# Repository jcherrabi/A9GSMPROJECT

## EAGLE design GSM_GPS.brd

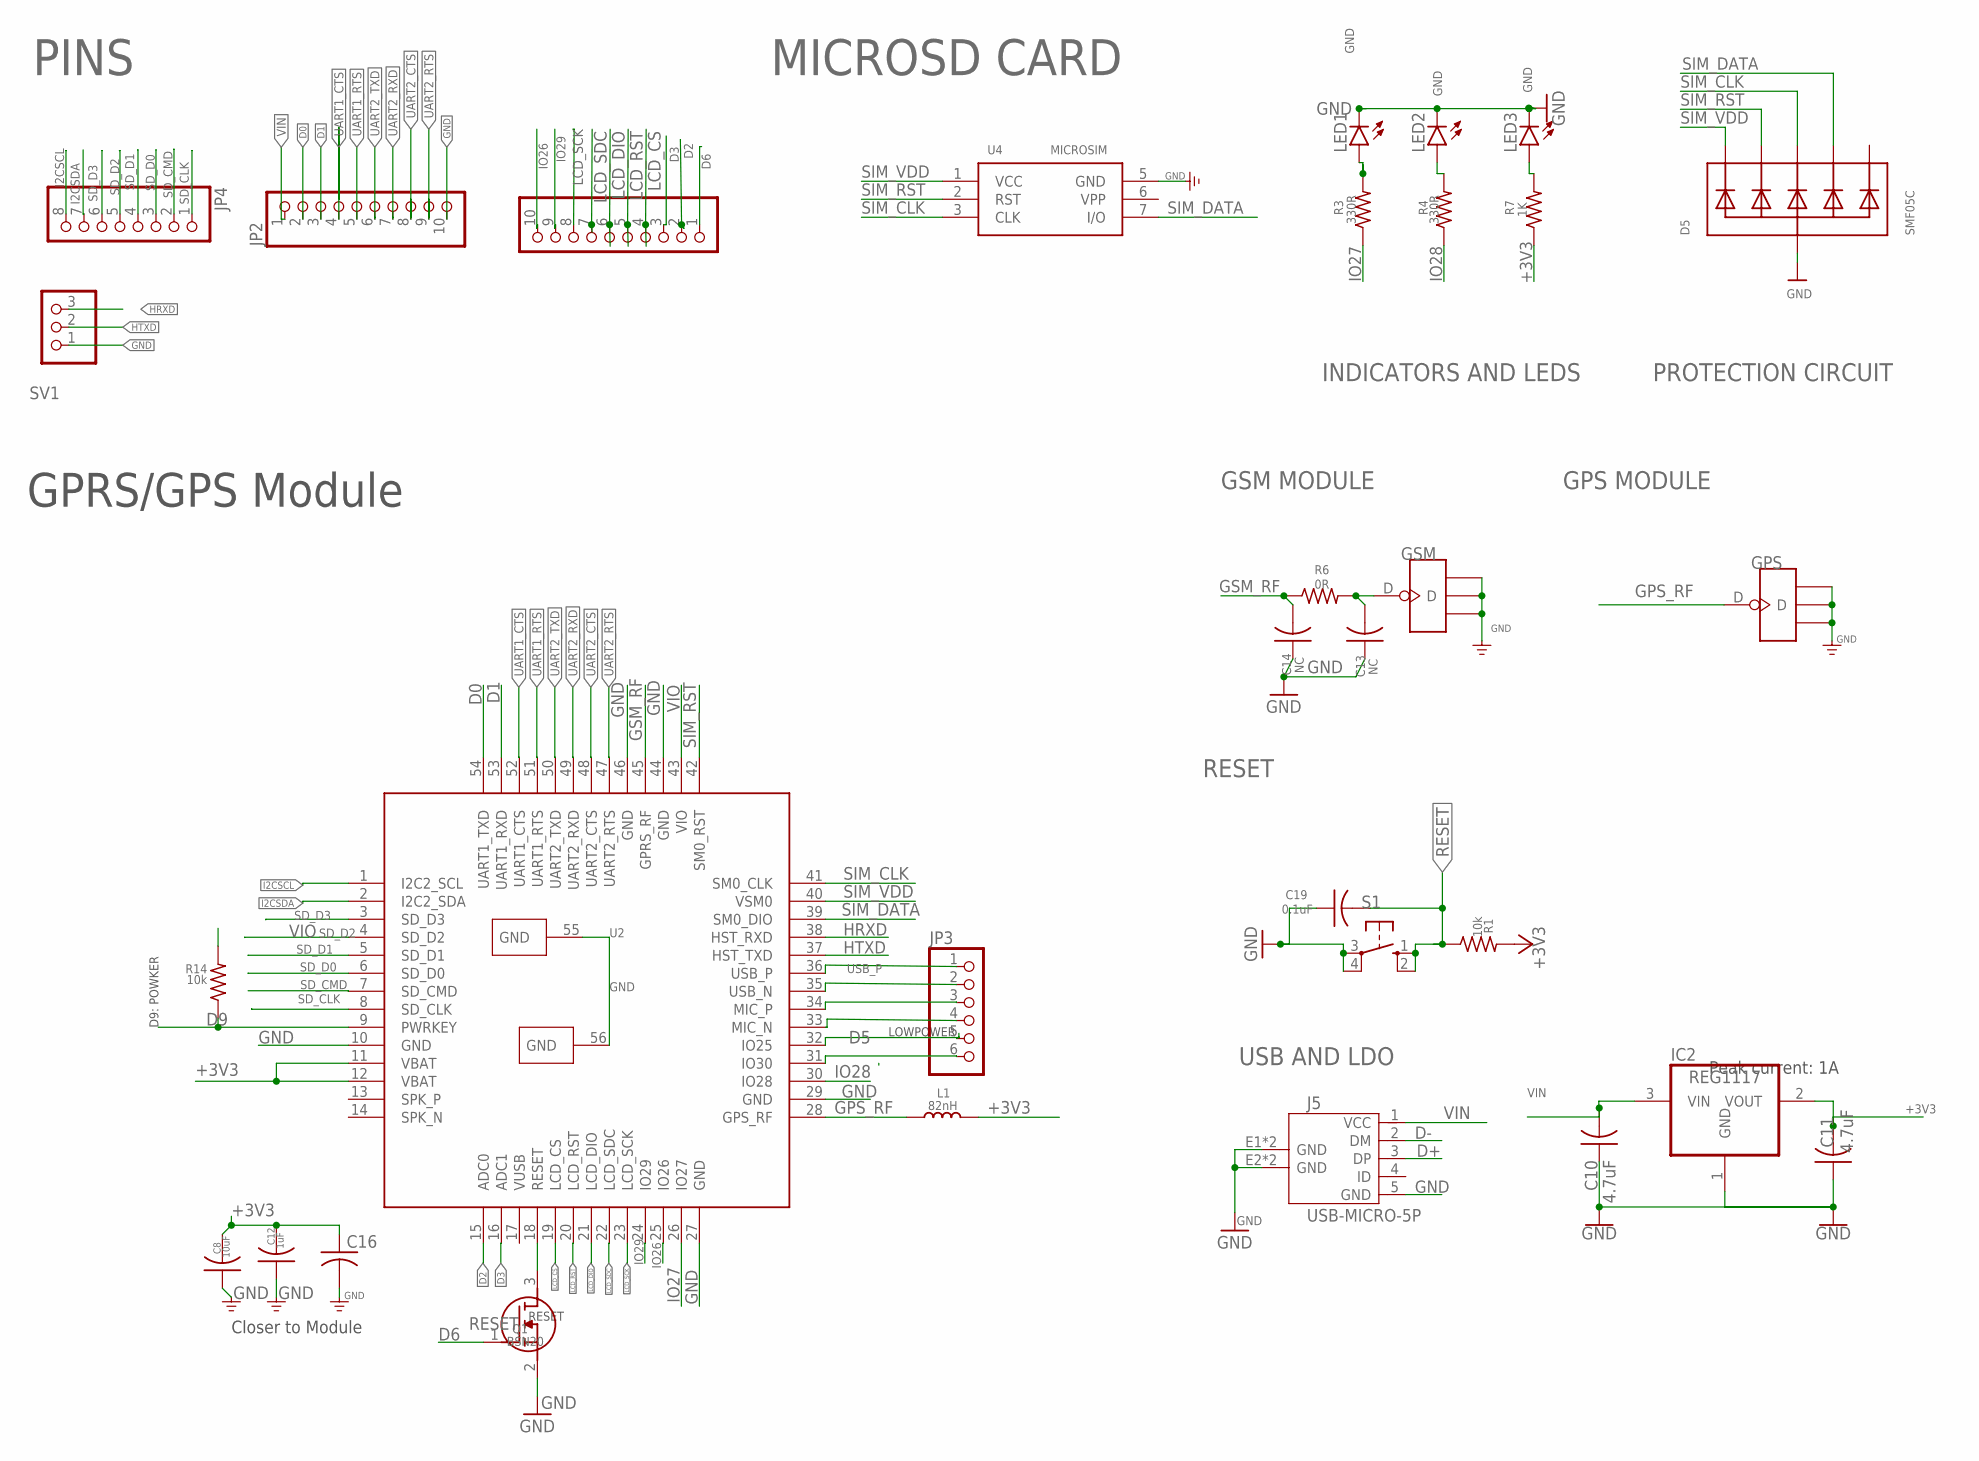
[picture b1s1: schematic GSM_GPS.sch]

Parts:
C8: 10uF; C0805
C10, C11: 4.7uF; C0805
C12: 1uF; C0805
C13, C14: NC; C0805
C16: 100uF; C0805
C19: 0.1uF; C0805
D5: SMF05C; SOT363
GPS: ANTENNA-U-FL; 4P-U-FL
GSM: ANTENNA-U-FL; 4P-U-FL
IC2: REG1117; SOT223
J2: PINHD-1X10; 1X10
J5: USB-MICRO-5P; MICRO-USB-5P
JP2: PINHD-1X10; 1X10
JP3: PINHD-1X6; 1X06
JP4: PINHD-1X8; 1X08
L1: 82nH; L0603
LED1, LED2, LED3: LEDCHIPLED_0805; CHIPLED_0805
Q1: BSN20; SOT95P237X112-3N
R1, R14: 10k; R0805
R3, R4: 330R; R0805
R6: 0R; R0805
R7: 1K; R0805
S1: 10-XX; B3F-10XX
SV1: PINHD-1X3; 1X03
U2: A9G
U4: MICROSIM

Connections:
+3V3: C8.2, C11.2, C12.2, C16.1, IC2.2 (VOUT), L1.2, R1.2, R7.1, U2.11 (VBAT), U2.12 (VBAT)
D0: JP2.2, U2.54 (UART1_TXD)
D1: JP2.3, U2.53 (UART1_RXD)
D2: J2.2, U2.15 (ADC0)
D3: J2.3, U2.16 (ADC1)
D5: JP3.5, U2.32 (IO25)
D6: J2.1, Q1.1 (G)
D9: R14.1, U2.9 (PWRKEY)
D+: J5.3 (DP)
D-: J5.2 (DM)
GND: C8.1, C10.1, C11.1, C12.1, C13.1, C14.1, C16.2, C19.1, D5.2 (A), GPS.GND1, GPS.GND2, GPS.GND3, GSM.GND1, GSM.GND2, GSM.GND3, IC2.1 (GND), J5.5 (GND), J5.E1 (GND), J5.E2 (GND), J5.P1 (GND), J5.P2 (GND), JP2.10, LED1.C, LED2.C, LED3.C, Q1.2 (S), S1.3, S1.4 (P1), SV1.1, U2.10 (GND), U2.27 (GND), U2.29 (GND), U2.44 (GND), U2.46 (GND), U2.55 (GND), U2.56 (GND), U4.5 (GND)
GPS_RF: GPS.D, L1.1, U2.28 (GPS_RF)
GSM_RF: C14.2, R6.1, U2.45 (GPRS_RF)
HRXD: SV1.3, U2.38 (HST_RXD)
HTXD: SV1.2, U2.37 (HST_TXD)
I2CSCL: JP4.8, U2.1 (I2C2_SCL)
I2CSDA: JP4.7, U2.2 (I2C2_SDA)
IO26: J2.10, U2.25 (IO26)
IO27: R3.1, U2.26 (IO27)
IO28: R4.1, U2.30 (IO28)
IO29: J2.9, U2.24 (IO29)
LCD_CS: J2.4, U2.19 (LCD_CS)
LCD_DIO: J2.6, U2.21 (LCD_DIO)
LCD_RST: J2.5, U2.20 (LCD_RST)
LCD_SCK: J2.8, U2.23 (LCD_SCK)
LCD_SDC: J2.7, U2.22 (LCD_SDC)
unnamed: LED2.A, R4.2
unnamed: JP3.6, U2.31 (IO30)
unnamed: LED3.A, R7.2
unnamed: JP3.3, U2.34 (MIC_P)
unnamed: JP3.4, U2.33 (MIC_N)
unnamed: LED1.A, R3.2
unnamed: JP3.2, U2.35 (USB_N)
unnamed: C13.2, GSM.D, R6.2
RESET: C19.2, Q1.3 (D), R1.1, S1.1 (S), S1.2 (S1), U2.18 (RESET)
SD_CLK: JP4.1, U2.8 (SD_CLK)
SD_CMD: JP4.2, U2.7 (SD_CMD)
SD_D0: JP4.3, U2.6 (SD_D0)
SD_D1: JP4.4, U2.5 (SD_D1)
SD_D2: JP4.5, U2.4 (SD_D2)
SD_D3: JP4.6, U2.3 (SD_D3)
SIM_CLK: D5.4 (C3), U2.41 (SM0_CLK), U4.3 (CLK)
SIM_DATA: D5.5 (C4), U2.39 (SM0_DIO), U4.7 (I/O)
SIM_RST: D5.3 (C2), U2.42 (SM0_RST), U4.2 (RST)
SIM_VDD: D5.1 (C1), U2.40 (VSM0), U4.1 (VCC)
UART1_CTS: JP2.4, U2.52 (UART1_CTS)
UART1_RTS: JP2.5, U2.51 (UART1_RTS)
UART2_CTS: JP2.8, U2.48 (UART2_CTS)
UART2_RTS: JP2.9, U2.47 (UART2_RTS)
UART2_RXD: JP2.7, U2.49 (UART2_RXD)
UART2_TXD: JP2.6, U2.50 (UART2_TXD)
USB_P: JP3.1, U2.36 (USB_P)
VIN: C10.2, IC2.3 (VIN), J5.1 (VCC), JP2.1
VIO: R14.2, U2.43 (VIO)

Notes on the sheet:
GPRS/GPS Module
LOWPOWER
RESET
D9: POWKER
Closer to Module
Peak current: 1A
PINS
MICROSD CARD
INDICATORS AND LEDS
PROTECTION CIRCUIT
GSM MODULE
GPS MODULE
USB AND LDO

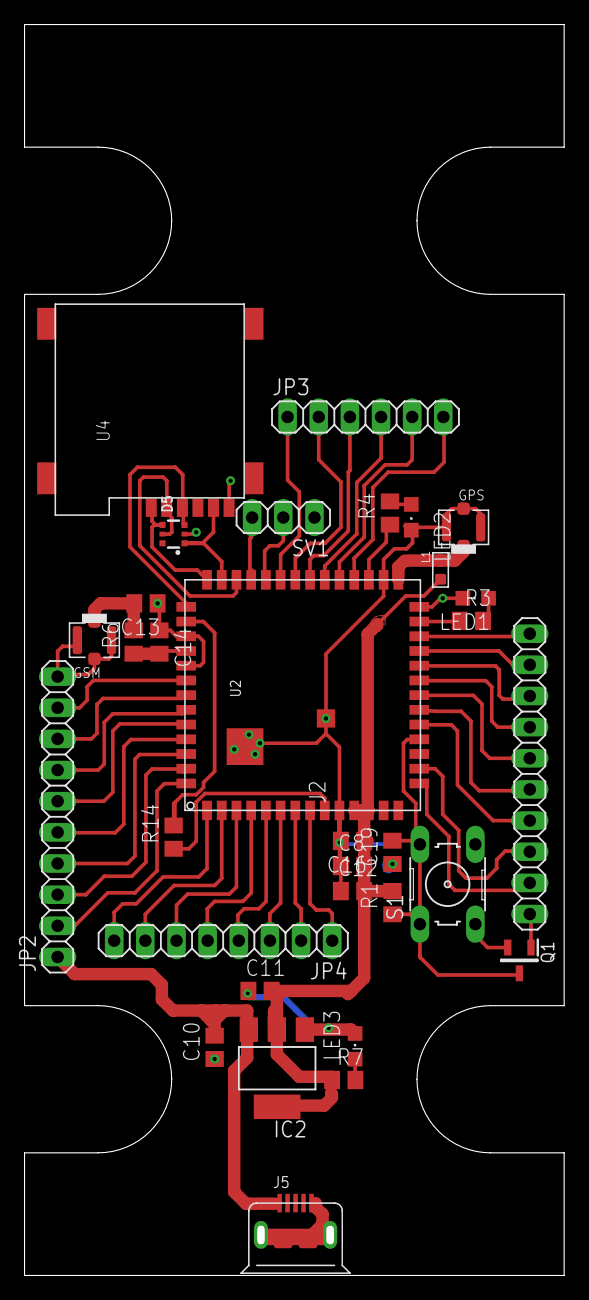
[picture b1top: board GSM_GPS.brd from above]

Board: 2 copper layers, 44.0 x 102.0 mm, 32 parts (0 on the bottom side), 52 nets.

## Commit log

2020-10-21 schematic
2020-10-21 placement
2020-10-22 board
2020-10-22 single sided pcb
2020-10-22 complete pcb : single sided :-)
2020-10-23 single sided pcb is ready for examination

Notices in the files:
parts and their libraries:
microbuilder: This work is placed in the public domain, and may be freely used for commercial and non-commercial work with the following conditions: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
SparkFun-PowerSymbols: Licensing: Creative Commons ShareAlike 4.0 International - https://creativecommons.org/licenses/by-sa/4.0
